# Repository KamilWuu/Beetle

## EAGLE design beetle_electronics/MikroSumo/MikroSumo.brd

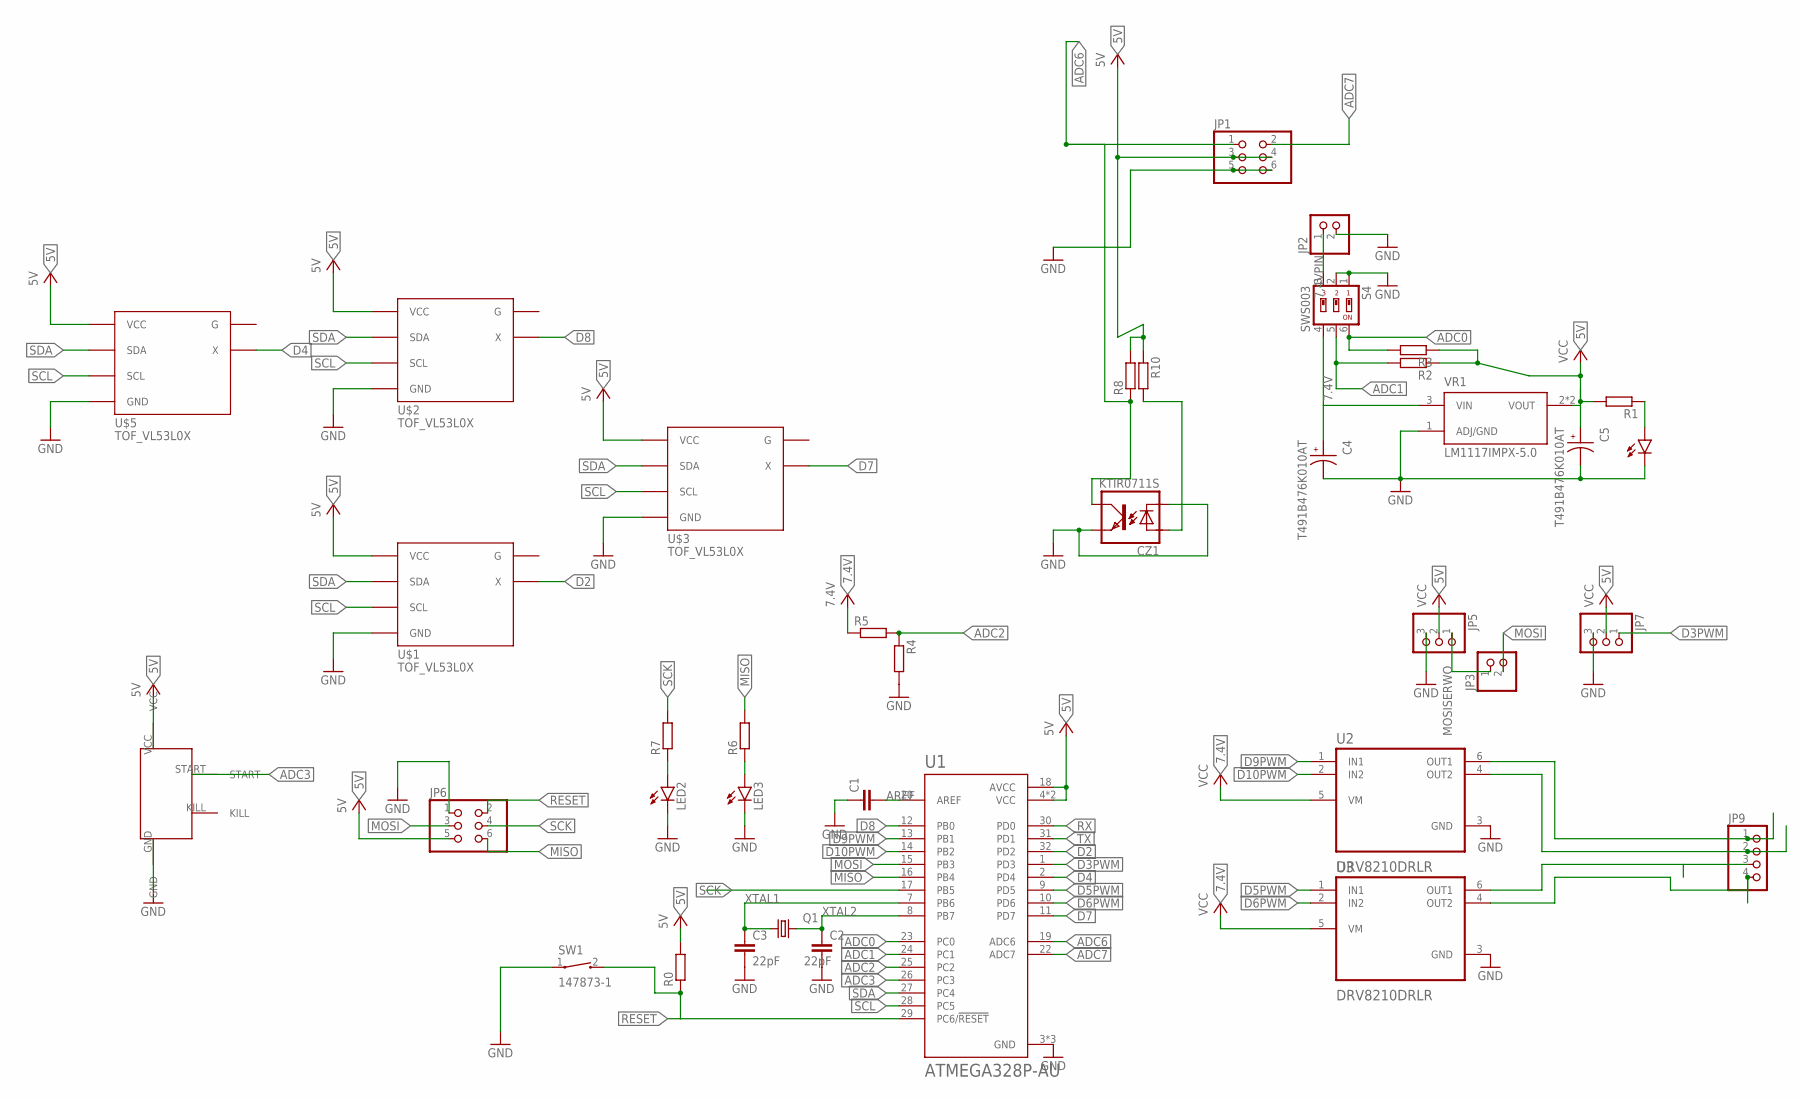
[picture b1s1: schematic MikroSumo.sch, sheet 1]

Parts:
C1: C-EUC0402; C0402
C2, C3: 22pF; C0402
C4, C5: T491B476K010AT; CAPPM3528X210N
CZ1: KTIR0711S; TOP
JP1, JP6: PINHD-2X3; 2X03
JP2, JP3: PINHD-1X2; 1X02
JP5, JP7: PINHD-1X3; 1X03
JP9: PINHD-1X4/90; 1X04/90
LED1, LED2, LED3: LEDCHIPLED_0603; CHIPLED_0603
Q1: KX-327-NHT; 3.2X1.5
R0, R1, R2, R3, R4, R5, R6, R7, R8, R10: R-EU_R0402; R0402
S4: SWS003; SMS-003
SW1: 147873-1; SW_147873-1
U1: ATMEGA328P-AU; QFP80P900X900X120-32N
U2, U3: DRV8210DRLR; SOT50P160X60-6N
U$1, U$2, U$3, U$5: TOF_VL53L0X
U$4: SUMO_START_MODULE
VR1: LM1117IMPX-5.0; SOT230P700X180-4N

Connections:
5V: C5.1, JP1.3, JP1.4, JP5.2, JP6.5, JP7.2, R0.2, R1.2, R2.1, R3.1, R8.2, R10.1, U1.4 (VCC), U1.6 (VCC), U1.18 (AVCC), U$1.VCC, U$1.VCC_ (VCC), U$2.VCC, U$2.VCC_ (VCC), U$3.VCC, U$3.VCC_ (VCC), U$4.VCC, U$5.VCC, U$5.VCC_ (VCC), VR1.2 (VOUT), VR1.4 (VOUT)
7.4V: C4.1, R5.1, S4.4, U2.5 (VM), U3.5 (VM), VR1.3 (VIN)
7.4VPIN: JP2.1, S4.3
ADC0: R3.2, S4.6, U1.23 (PC0)
ADC1: R2.2, S4.5, U1.24 (PC1)
ADC2: R4.1, R5.2, U1.25 (PC2)
ADC3: U1.26 (PC3), U$4.START
ADC6: CZ1.KOLEKTOR, JP1.1, R8.1, U1.19 (ADC6)
ADC7: JP1.2, U1.22 (ADC7)
AREF: C1.2, U1.20 (AREF); also elsewhere on the board
D2: U1.32 (PD2), U$1.X
D3PWM: JP7.1, U1.1 (PD3)
D4: U1.2 (PD4), U$5.X
D5PWM: U1.9 (PD5), U3.1 (IN1)
D6PWM: U1.10 (PD6), U3.2 (IN2)
D7: U1.11 (PD7), U$3.X
D8: U1.12 (PB0), U$2.X
D9PWM: U1.13 (PB1), U2.1 (IN1)
D10PWM: U1.14 (PB2), U2.2 (IN2)
GND: C1.1, C2.2, C3.2, C4.2, C5.2, CZ1.EMITER, CZ1.KATODA, JP1.5, JP1.6, JP2.2, JP5.3, JP6.1, JP7.3, LED1.C, LED2.C, LED3.C, R4.2, S4.1, S4.2, SW1.1, U1.3 (GND), U1.5 (GND), U1.21 (GND), U2.3 (GND), U3.3 (GND), U$1.GND, U$1.GND_ (GND), U$2.GND, U$2.GND_ (GND), U$3.GND, U$3.GND_ (GND), U$4.GND, U$5.GND, U$5.GND_ (GND), VR1.1 (ADJ/GND); also elsewhere on the board
MISO: JP6.6, R6.2, U1.16 (PB4); also elsewhere on the board
MOSI: JP3.2, JP6.3, U1.15 (PB3)
MOSISERWO: JP3.1, JP5.1
unnamed: JP9.1, U2.6 (OUT1)
unnamed: JP9.2, U2.4 (OUT2)
unnamed: JP9.3, U3.6 (OUT1)
unnamed: JP9.4, U3.4 (OUT2)
unnamed: LED1.A, R1.1
unnamed: LED3.A, R6.1
unnamed: LED2.A, R7.1
unnamed: CZ1.ANODA, R10.2
RESET: JP6.2, R0.1, SW1.2, U1.29 (PC6/!RESET); also elsewhere on the board
RX: U1.30 (PD0)
SCK: JP6.4, R7.2, U1.17 (PB5)
SCL: U1.28 (PC5), U$1.SCL, U$1.SCL_ (SCL), U$2.SCL, U$2.SCL_ (SCL), U$3.SCL, U$3.SCL_ (SCL), U$5.SCL, U$5.SCL_ (SCL)
SDA: U1.27 (PC4), U$1.SDA, U$1.SDA_ (SDA), U$2.SDA, U$2.SDA_ (SDA), U$3.SDA, U$3.SDA_ (SDA), U$5.SDA, U$5.SDA_ (SDA)
TX: U1.31 (PD1)
XTAL1: C3.1, Q1.1, U1.7 (PB6)
XTAL2: C2.1, Q1.2, U1.8 (PB7)

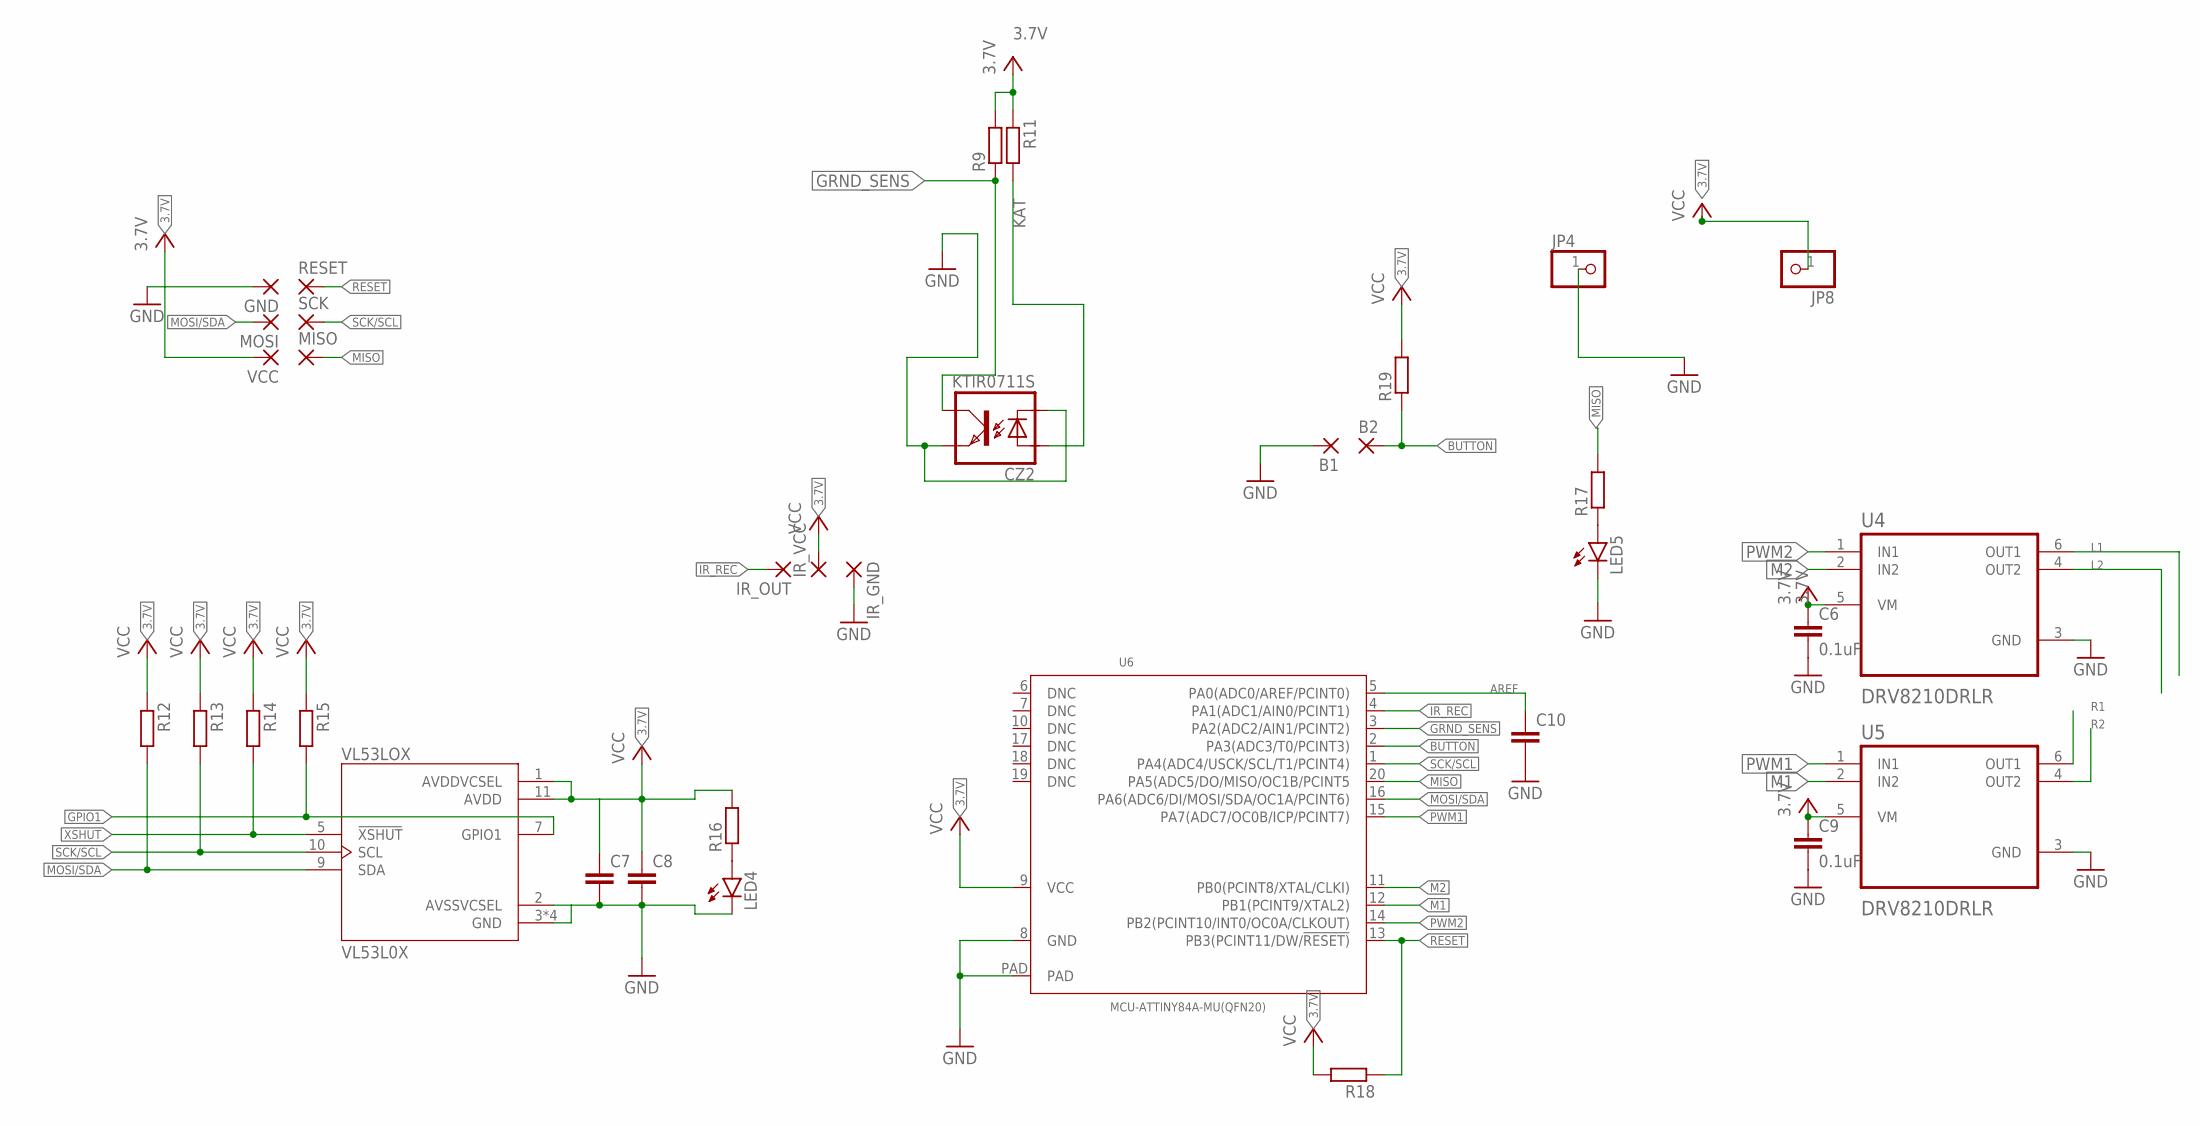
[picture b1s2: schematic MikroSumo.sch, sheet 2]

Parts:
B1, B2: SMD2; SMD1,27-2,54
C6, C9: 0.1uF; C0402
C7, C8, C10: C-EUC0402; C0402
CZ2: KTIR0711S; TOP
GND: SMD2; SMD1,27-2,54
IR_GND: SMD2; SMD1,27-2,54
IR_OUT: SMD2; SMD1,27-2,54
IR_VCC: SMD2; SMD1,27-2,54
JP4, JP8: PINHD-1X1; 1X01
LED4, LED5: LEDCHIP-LED0603; CHIP-LED0603
MISO: SMD2; SMD1,27-2,54
MOSI: SMD2; SMD1,27-2,54
R9, R11, R12, R13, R14, R15, R16, R17, R18, R19: R-EU_R0402; R0402
RESET: SMD2; SMD1,27-2,54
SCK: SMD2; SMD1,27-2,54
U4, U5: DRV8210DRLR; SOT50P160X60-6N
U6: MCU-ATTINY84A-MU(QFN20); QFN20G-0.5-4X4MM
VCC: SMD2; SMD1,27-2,54
VL53LOX: VL53L0X; SENSOR_VL53L0X

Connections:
3.7V: C6.1, C7.1, C8.1, C9.1, IR_VCC.1, JP8.1, R9.2, R11.1, R12.1, R13.1, R14.1, R15.1, R16.2, R18.2, R19.2, U4.5 (VM), U5.5 (VM), U6.9 (VCC), VCC.1, VL53LOX.1 (AVDDVCSEL), VL53LOX.11 (AVDD)
AREF: C10.1, U6.5 (PA0(ADC0/AREF/PCINT0)); also elsewhere on the board
BUTTON: B2.1, R19.1, U6.2 (PA3(ADC3/T0/PCINT3))
GND: B1.1, C6.2, C7.2, C8.2, C9.2, C10.2, CZ2.EMITER, CZ2.KATODA, GND.1, IR_GND.1, JP4.1, LED4.C, LED5.C, U4.3 (GND), U5.3 (GND), U6.8 (GND), U6.PAD, VL53LOX.2 (AVSSVCSEL), VL53LOX.3 (GND), VL53LOX.4 (GND), VL53LOX.6 (GND), VL53LOX.12 (GND); also elsewhere on the board
GPIO1: R15.2, VL53LOX.7 (GPIO1)
GRND_SENS: CZ2.KOLEKTOR, R9.1, U6.3 (PA2(ADC2/AIN1/PCINT2))
IR_REC: IR_OUT.1, U6.4 (PA1(ADC1/AIN0/PCINT1))
KAT: CZ2.ANODA, R11.2
L1: U4.6 (OUT1)
L2: U4.4 (OUT2)
M1: U5.2 (IN2), U6.12 (PB1(PCINT9/XTAL2))
M2: U4.2 (IN2), U6.11 (PB0(PCINT8/XTAL/CLKI))
MISO: MISO.1, R17.2, U6.20 (PA5(ADC5/DO/MISO/OC1B/PCINT5); also elsewhere on the board
MOSI/SDA: MOSI.1, R12.2, U6.16 (PA6(ADC6/DI/MOSI/SDA/OC1A/PCINT6)), VL53LOX.9 (SDA)
unnamed: LED4.A, R16.1
unnamed: LED5.A, R17.1
PWM1: U5.1 (IN1), U6.15 (PA7(ADC7/OC0B/ICP/PCINT7))
PWM2: U4.1 (IN1), U6.14 (PB2(PCINT10/INT0/OC0A/CLKOUT))
R1: U5.6 (OUT1)
R2: U5.4 (OUT2)
RESET: R18.1, RESET.1, U6.13 (PB3(PCINT11/DW/!RESET)); also elsewhere on the board
SCK/SCL: R13.2, SCK.1, U6.1 (PA4(ADC4/USCK/SCL/T1/PCINT4)), VL53LOX.10 (SCL)
XSHUT: R14.2, VL53LOX.5 (!XSHUT)

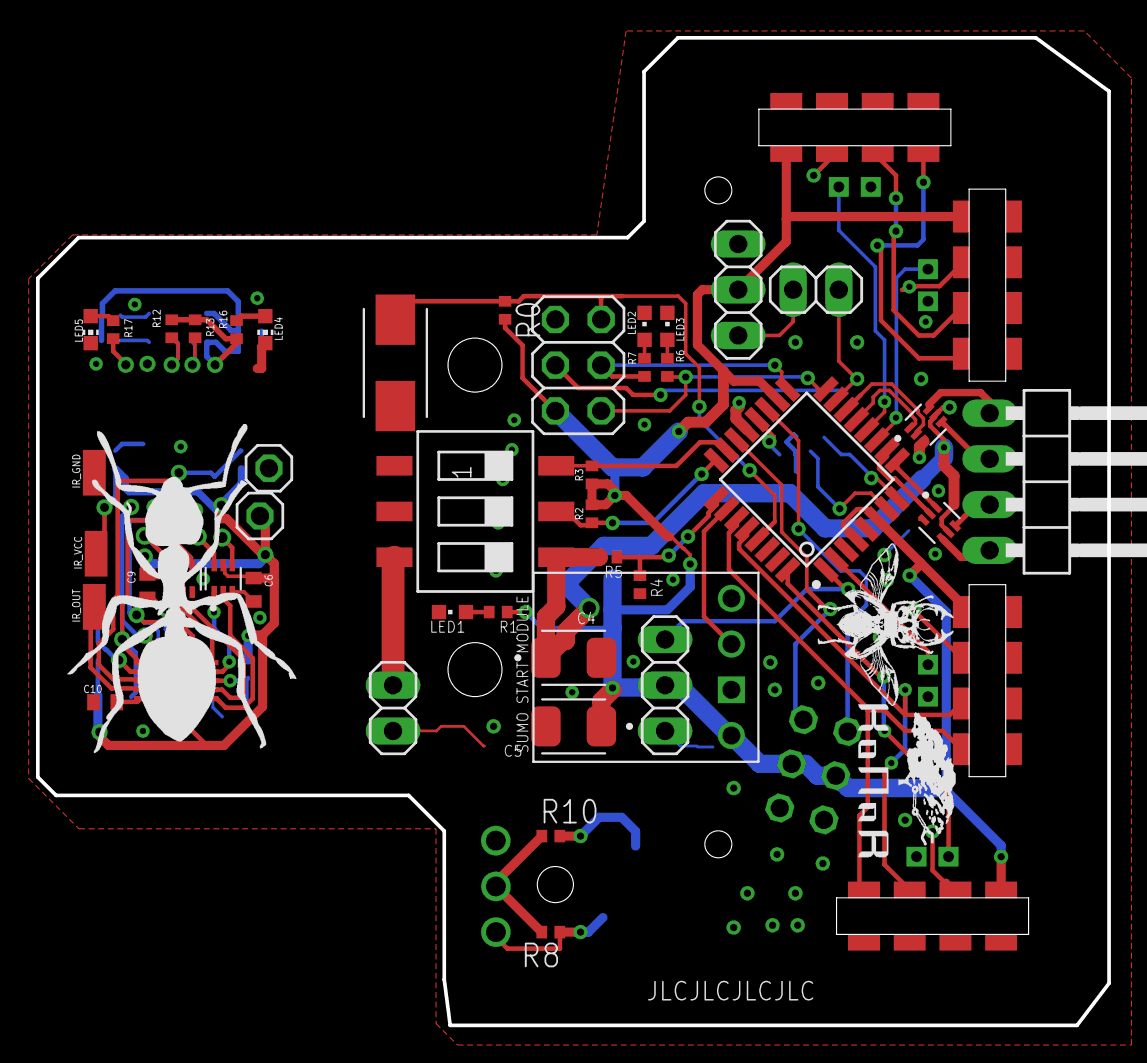
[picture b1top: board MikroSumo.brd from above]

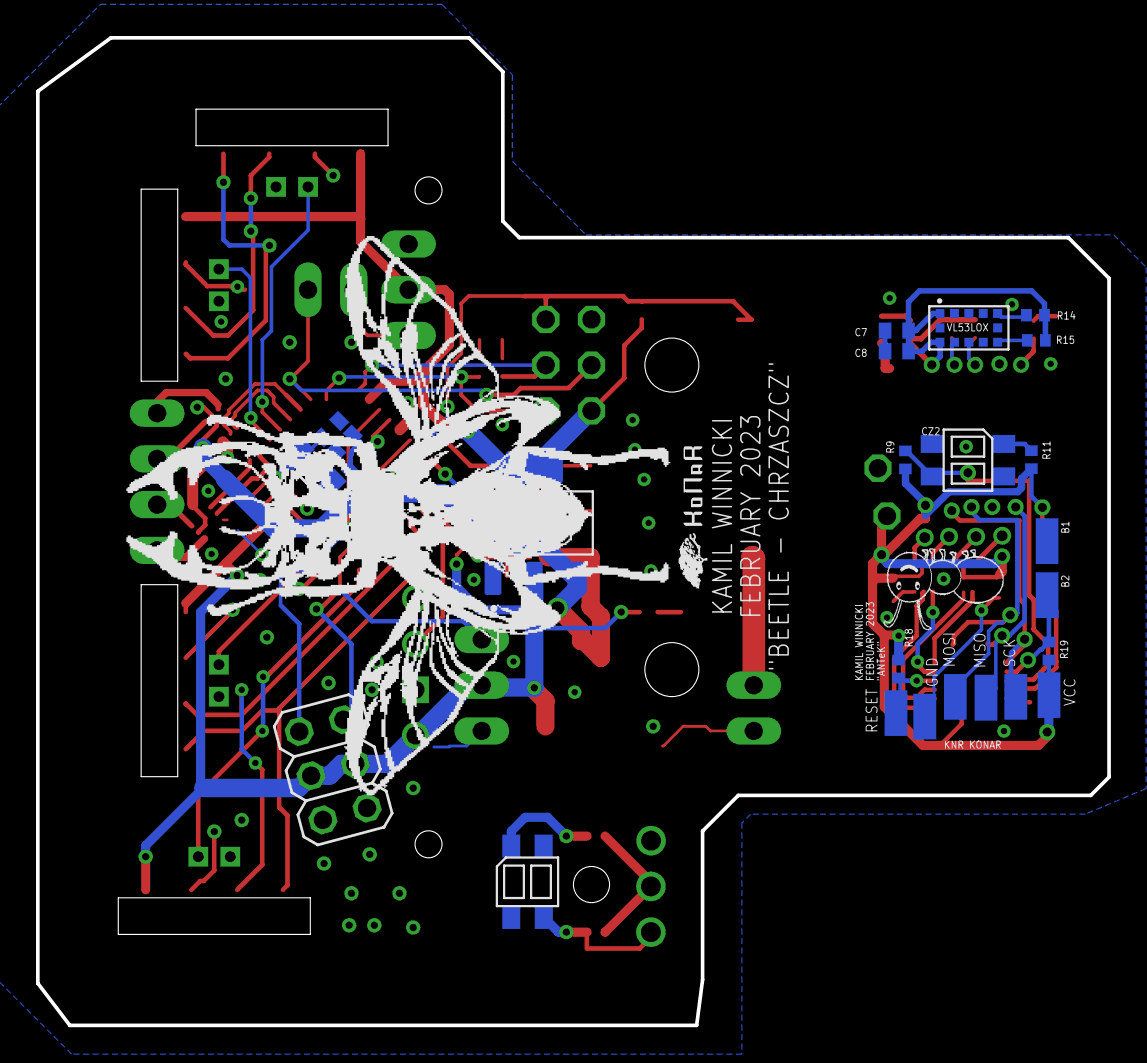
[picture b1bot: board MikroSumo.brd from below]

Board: 2 copper layers, 59.5 x 54.9 mm, 73 parts (25 on the bottom side), 52 nets.

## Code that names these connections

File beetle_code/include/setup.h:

#pragma once
#include <Arduino.h>


//----LEDS----//
#define LED_RED 13 //PB5
#define LED_BLUE 12 //PB4

//----MOTORS----//
#define MOTOR_LEFT_FORWARD 10 //PB2
#define MOTOR_LEFT_BACK 9  //PB1

#define MOTOR_RIGHT_FORWARD 6 //PD6
#define MOTOR_RIGHT_BACK 5 //PD5

//----SERVOS----//
#define SERVO_LEFT 11 //PB3
#define SERVO_RIGHT 3 //PD3

//----TOF_XSHUTS----//
#define XSHUT_TOF_1 8 //PB0
#define XSHUT_TOF_2 7 //PD7
#define XSHUT_TOF_3 4 //PD4
#define XSHUT_TOF_4 2 //PD2

//----GROUND_SENSORS----//
#define GROUND_SENSOR_LEFT A7
#define GROUND_SENSOR_RIGHT A6

//----SWITCHES----//
#define SWITCH_1 A0
#define SWITCH_2 A1

//----STARTER----//
#define STARTER A3

//----VOLTAGE_MEASUREMENT----//
#define VOLTAGE A2
#define MIN_VOLTAGE 780 // x = 7,5 (minimal) * 10/20,,, 1023*x/5 = 770

void pinModes();
void voltageBlink(uint16_t onT, uint16_t offT);

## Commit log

2023-02-24 Utworzono repozytorium
2023-02-24 dodano readme
2023-02-28 Utworzono kod i definicje pinow
2023-02-28 zmieniono folder mechaniki
2023-02-28 Test gita w vscode
2023-02-28 "test gita w vscode"
2023-03-07 Dodano obsluge tofow V 0.0
2023-03-08 Dodano dzialajace tofy
2023-03-09 TOF dobre i dzialajace
2023-03-10 zmieniono tof.h/cpp na klasy, dodano state.h/cpp
2023-03-11 dodano fight
2023-03-12 dodano ustawienie flag i odczytanie stanow
2023-06-19 some changes

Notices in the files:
parts and their libraries:
crystal-geyer_V1_0: Copyright: Geyer-Electronic
